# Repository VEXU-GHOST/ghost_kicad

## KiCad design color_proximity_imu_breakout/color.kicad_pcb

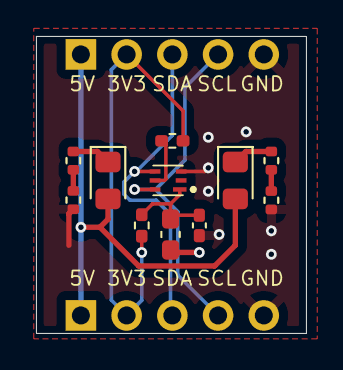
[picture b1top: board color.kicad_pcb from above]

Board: 2 copper layers, 15.0 x 16.5 mm, 13 parts (0 on the bottom side), 11 nets.

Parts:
C4: 1u; C_0603_1608Metric_Pad1.08x0.95mm_HandSolder
C5: 0.1u; C_0402_1005Metric_Pad0.74x0.62mm_HandSolder
D1, D2: WHITE; LED_0805_2012Metric_Pad1.15x1.40mm_HandSolder
IC2: ISL29125IROZ-T7; ISL29125IROZT7
J4, J4#2: Conn_01x05; PinHeader_1x05_P2.54mm_Vertical
R15: 100; R_0402_1005Metric_Pad0.72x0.64mm_HandSolder
R16: 4.7k; R_0402_1005Metric_Pad0.72x0.64mm_HandSolder
R17, R18, R30, R32: 120; R_0402_1005Metric

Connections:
+3.3V: J4.2, J4#2.2, R15.2, R16.1
+5V: D1.2 (A), D2.2 (A), J4.1, J4#2.1
/scl: IC2.6 (SCL), J4.4, J4#2.4
/sda: IC2.4 (SDA), J4.3, J4#2.3
GND: C4.2, C5.2, IC2.3 (GND), J4.5, J4#2.5, R30.2, R32.2
unnamed: D1.1 (K), R17.1
unnamed: D2.1 (K), R18.1
unnamed: C4.1, C5.1, IC2.1 (VDD), R15.1
unnamed: IC2.5 (~INT), R16.2
unnamed: R17.2, R30.1
unnamed: R18.2, R32.1

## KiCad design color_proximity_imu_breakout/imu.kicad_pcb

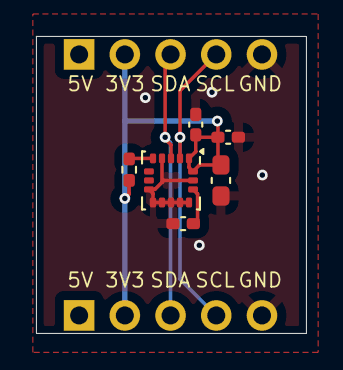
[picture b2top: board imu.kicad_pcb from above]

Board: 2 copper layers, 15.0 x 16.5 mm, 8 parts (0 on the bottom side), 7 nets.

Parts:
C7, C10: 0.1u; C_0402_1005Metric_Pad0.74x0.62mm_HandSolder
C8: 2.2u; C_0603_1608Metric_Pad1.08x0.95mm_HandSolder
C9: 10n; C_0402_1005Metric_Pad0.74x0.62mm_HandSolder
J4, J4#2: Conn_01x05; PinHeader_1x05_P2.54mm_Vertical
R19: 4.7k; R_0402_1005Metric_Pad0.72x0.64mm_HandSolder
U6: ICM-20602; LGA-16_3x3mm_P0.5mm_LayoutBorder3x5y

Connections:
+3.3V: C7.1, C8.1, C9.1, J4.2, J4#2.2, R19.1, U6.1 (VDDIO), U6.16 (VDD)
+5V: J4.1, J4#2.1
/scl: J4.4, J4#2.4, U6.2 (SCL/SPC)
/sda: J4.3, J4#2.3, U6.3 (SDA/SDI)
GND: C7.2, C8.2, C9.2, C10.2, J4.5, J4#2.5, U6.4 (SAO/SD0), U6.8 (FSYNC), U6.9 (GND), U6.10 (GND), U6.11 (GND), U6.12 (GND), U6.13 (GND), U6.15 (GND)
unnamed: C10.1, U6.14 (REGOUT)
unnamed: R19.2, U6.5 (~CS)

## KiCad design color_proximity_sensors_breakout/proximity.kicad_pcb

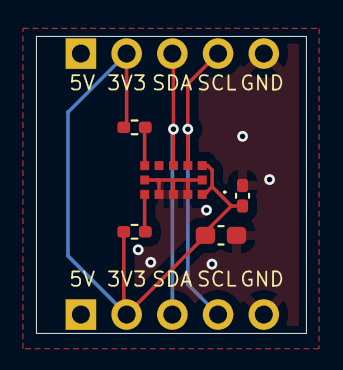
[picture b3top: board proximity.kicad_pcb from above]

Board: 2 copper layers, 15.0 x 16.5 mm, 7 parts (0 on the bottom side), 7 nets.

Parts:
C11: 0.1u; C_0402_1005Metric_Pad0.74x0.62mm_HandSolder
C12: 4.7u; C_0603_1608Metric_Pad1.08x0.95mm_HandSolder
IC1: VL53L4CDV0DH_1; VL53L4CDV0DH1
J4, J4#2: Conn_01x05; PinHeader_1x05_P2.54mm_Vertical
R20, R21: 10k; R_0402_1005Metric_Pad0.72x0.64mm_HandSolder

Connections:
+3.3V: C11.1, C12.1, IC1.1 (AVDDVCSEL_1), IC1.11 (AVDD), IC1.13 (AVDDVCSEL_2), J4.2, J4#2.2, R20.2, R21.1
+5V: J4.1, J4#2.1
/scl: IC1.10 (SCL), J4.4, J4#2.4
/sda: IC1.9 (SDA), J4.3, J4#2.3
GND: C11.2, C12.2, IC1.2 (AVSSVCSEL), IC1.3 (GND), IC1.4 (GND2), IC1.6 (GND3), IC1.12 (GND4), J4.5, J4#2.5
unnamed: IC1.7 (GPIO1), R20.1
unnamed: IC1.5 (XSHUT), R21.2

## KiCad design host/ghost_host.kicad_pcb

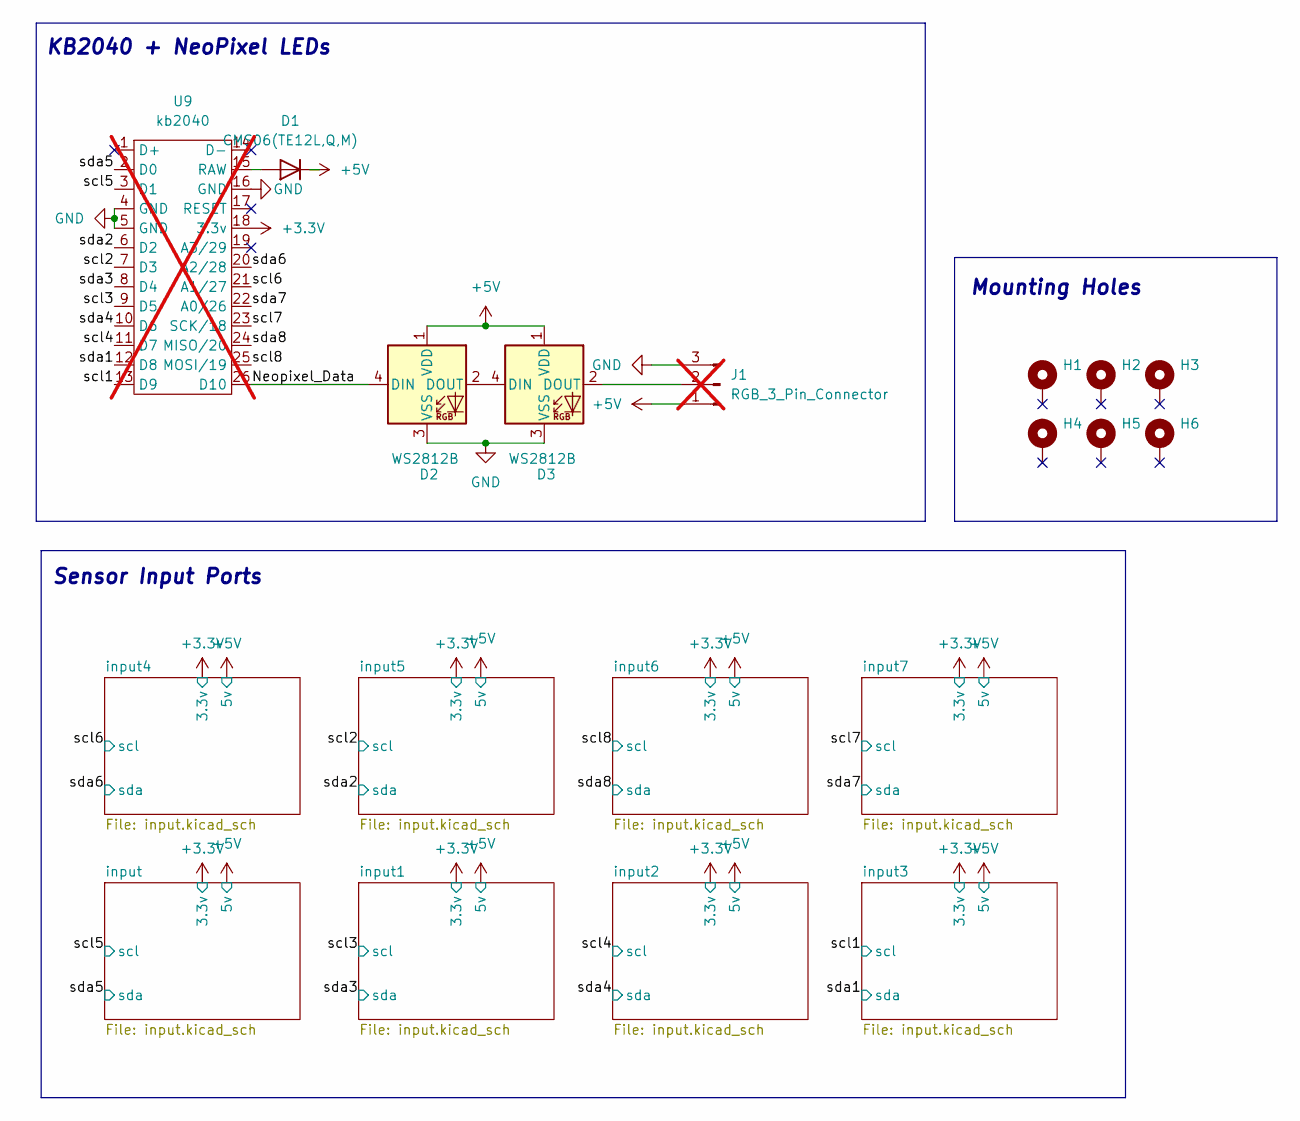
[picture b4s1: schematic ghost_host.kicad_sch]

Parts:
D1: CMS06(TE12L,Q,M); D_SOD-128; Manufacturer Part Number CMS06(TE12L,Q,M)
D2, D3: WS2812B; LED_WS2812B_PLCC4_5.0x5.0mm_P3.2mm; Manufacturer Part Number XL-5050RGBC-2812B
H1, H2, H3, H4, H5, H6: MountingHole_Pad; MountingHole_4.5mm_Pad_Via
J1: RGB_3_Pin_Connector; PinHeader_1x03_P2.54mm_Horizontal; not fitted
U9: kb2040; Manufacturer Part Number 5302; not fitted

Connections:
+3.3V: U9.18 (3.3v); also elsewhere on the board
+5V: D1.1 (K), D2.1 (VDD), D3.1 (VDD), J1.1; also elsewhere on the board
/Neopixel_Data: D2.4 (DIN), U9.26 (D10)
/scl1: U9.13 (D9); also elsewhere on the board
/scl2: U9.7 (D3); also elsewhere on the board
/scl3: U9.9 (D5); also elsewhere on the board
/scl4: U9.11 (D7); also elsewhere on the board
/scl5: U9.3 (D1); also elsewhere on the board
/scl6: U9.21 (A1/27); also elsewhere on the board
/scl7: U9.23 (SCK/18); also elsewhere on the board
/scl8: U9.25 (MOSI/19); also elsewhere on the board
/sda1: U9.12 (D8); also elsewhere on the board
/sda2: U9.6 (D2); also elsewhere on the board
/sda3: U9.8 (D4); also elsewhere on the board
/sda4: U9.10 (D6); also elsewhere on the board
/sda5: U9.2 (D0); also elsewhere on the board
/sda6: U9.20 (A2/28); also elsewhere on the board
/sda7: U9.22 (A0/26); also elsewhere on the board
/sda8: U9.24 (MISO/20); also elsewhere on the board
GND: D2.3 (VSS), D3.3 (VSS), J1.3, U9.4 (GND), U9.5 (GND), U9.16 (GND); also elsewhere on the board
unnamed: D1.2 (A), U9.15 (RAW)
unnamed: D2.2 (DOUT), D3.4 (DIN)
unnamed: D3.2 (DOUT), J1.2

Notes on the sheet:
KB2040 + NeoPixel LEDs
Mounting Holes
Sensor Input Ports

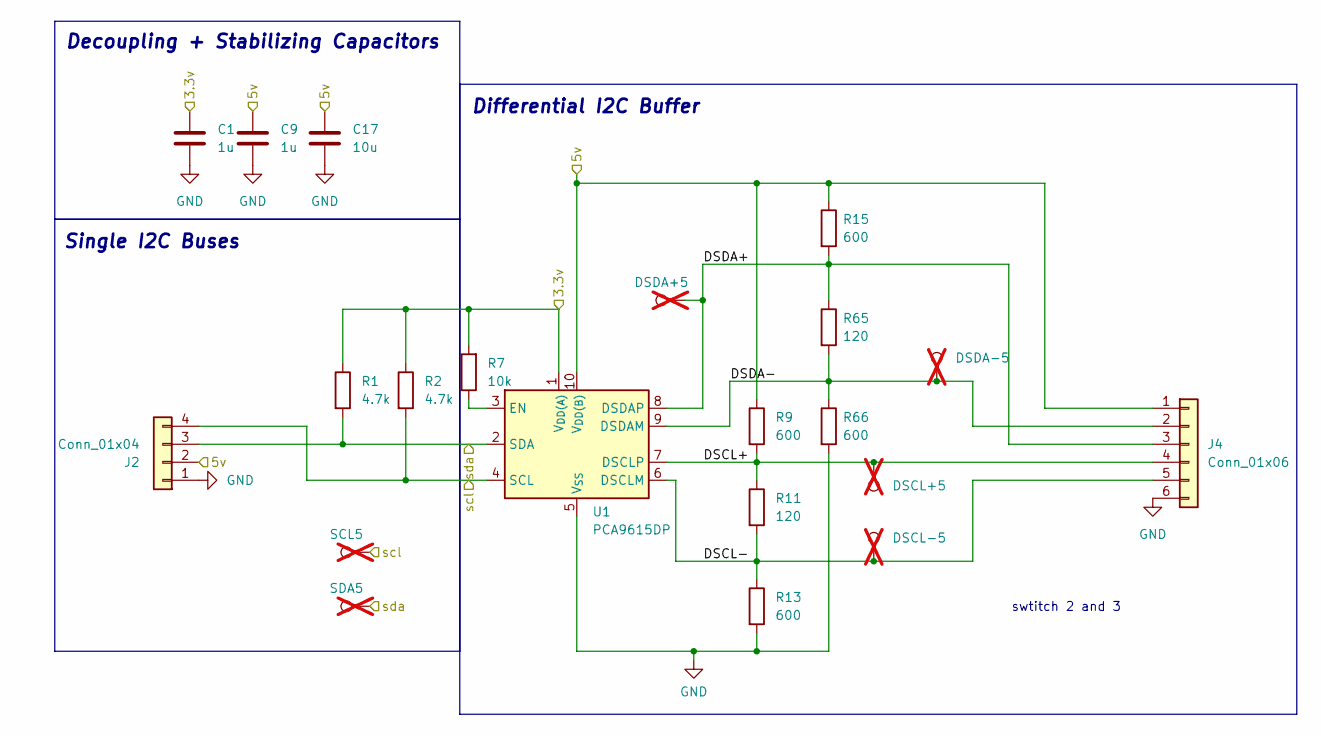
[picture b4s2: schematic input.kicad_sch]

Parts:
C1, C9: 1u; C_0603_1608Metric; Manufacturer Part Number CL10B105KB8NQNC
C17: 10u; C_0603_1608Metric; Manufacturer Part Number CL10A106KP8NNNC
DSCL+5: TestPoint; TestPoint_THTPad_1.0x1.0mm_Drill0.5mm; not fitted
DSCL-5: TestPoint; TestPoint_THTPad_1.0x1.0mm_Drill0.5mm; not fitted
DSDA+5: TestPoint; TestPoint_THTPad_1.0x1.0mm_Drill0.5mm; not fitted
DSDA-5: TestPoint; TestPoint_THTPad_1.0x1.0mm_Drill0.5mm; not fitted
J2: Conn_01x04; JST_GH_BM04B-GHS-TBT_1x04-1MP_P1.25mm_Vertical; Manufacturer Part Number BM04B-GHS-TBT(LF)(SN)
J4: Conn_01x06; JST_GH_SM06B-GHS-TB_1x06-1MP_P1.25mm_Horizontal; Manufacturer Part Number XY-SM06B-GHS-TB
R1, R2: 4.7k; R_0603_1608Metric_Pad0.98x0.95mm_HandSolder; Manufacturer Part Number 0603WAF4701T5E
R7: 10k; R_0603_1608Metric_Pad0.98x0.95mm_HandSolder; Manufacturer Part Number 0603WAF1002T5E
R9, R13, R15, R66: 600; R_0603_1608Metric_Pad0.98x0.95mm_HandSolder; Manufacturer Part Number 0603WAF5600T5E
R11, R65: 120; R_0603_1608Metric_Pad0.98x0.95mm_HandSolder; Manufacturer Part Number 0603WAF1200T5E
SCL5: TestPoint; TestPoint_THTPad_1.0x1.0mm_Drill0.5mm; not fitted
SDA5: TestPoint; TestPoint_THTPad_1.0x1.0mm_Drill0.5mm; not fitted
U1: PCA9615DP; TSSOP-10_3x3mm_P0.5mm; Manufacturer Part Number PCA9615DPZ

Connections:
+3.3V: C1.1, R1.1, R2.1, R7.2, U1.1 (V_{DD(A)}); also elsewhere on the board
+5V: C9.1, C17.1, J2.2, J4.1, R9.1, R15.1, U1.10 (V_{DD(B)}); also elsewhere on the board
/input/DSCL+: DSCL+5.1, J4.4, R9.2, R11.1, U1.7 (DSCLP)
/input/DSCL-: DSCL-5.1, J4.5, R11.2, R13.1, U1.6 (DSCLM)
/input/DSDA+: DSDA+5.1, J4.3, R15.2, R65.1, U1.8 (DSDAP)
/input/DSDA-: DSDA-5.1, J4.2, R65.2, R66.1, U1.9 (DSDAM)
/scl5: J2.4, R2.2, SCL5.1, U1.4 (SCL); also elsewhere on the board
/sda5: J2.3, R1.2, SDA5.1, U1.2 (SDA); also elsewhere on the board
GND: C1.2, C9.2, C17.2, J2.1, J4.6, R13.2, R66.2, U1.5 (V_{SS}); also elsewhere on the board
unnamed: R7.1, U1.3 (EN)

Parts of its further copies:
C2, C3, C4, C5, C6, C7, C8, C10, C11, C12, C13, C14, C15, C16: 1u; C_0603_1608Metric; Manufacturer Part Number CL10B105KB8NQNC
C18, C19, C20, C21, C22, C23, C24: 10u; C_0603_1608Metric; Manufacturer Part Number CL10A106KP8NNNC
DSCL+1, DSCL+2, DSCL+3, DSCL+4, DSCL+6, DSCL+7, DSCL+8: TestPoint; TestPoint_THTPad_1.0x1.0mm_Drill0.5mm; not fitted
DSCL-1, DSCL-2, DSCL-3, DSCL-4, DSCL-6, DSCL-7, DSCL-8: TestPoint; TestPoint_THTPad_1.0x1.0mm_Drill0.5mm; not fitted
DSDA+1, DSDA+2, DSDA+3, DSDA+4, DSDA+6, DSDA+7, DSDA+8: TestPoint; TestPoint_THTPad_1.0x1.0mm_Drill0.5mm; not fitted
DSDA-1, DSDA-2, DSDA-3, DSDA-4, DSDA-6, DSDA-7, DSDA-8: TestPoint; TestPoint_THTPad_1.0x1.0mm_Drill0.5mm; not fitted
J3, J5, J8, J11, J14, J17, J20: Conn_01x04; JST_GH_BM04B-GHS-TBT_1x04-1MP_P1.25mm_Vertical; Manufacturer Part Number BM04B-GHS-TBT(LF)(SN)
J6, J9, J12, J15, J18, J21, J23: Conn_01x06; JST_GH_SM06B-GHS-TB_1x06-1MP_P1.25mm_Horizontal; Manufacturer Part Number XY-SM06B-GHS-TB
R3, R14, R19, R21, R22, R24, R26, R28, R32, R34, R35, R37, R41, R43, R44, R46, R50, R52, R53, R55, R59, R61, R62, R64, R67, R69, R70, R72: 600; R_0603_1608Metric_Pad0.98x0.95mm_HandSolder; Manufacturer Part Number 0603WAF5600T5E
R4, R5, R8, R10, R16, R17, R29, R30, R38, R39, R47, R48, R56, R57: 4.7k; R_0603_1608Metric_Pad0.98x0.95mm_HandSolder; Manufacturer Part Number 0603WAF4701T5E
R6, R12, R18, R31, R40, R49, R58: 10k; R_0603_1608Metric_Pad0.98x0.95mm_HandSolder; Manufacturer Part Number 0603WAF1002T5E
R20, R23, R25, R27, R33, R36, R42, R45, R51, R54, R60, R63, R68, R71: 120; R_0603_1608Metric_Pad0.98x0.95mm_HandSolder; Manufacturer Part Number 0603WAF1200T5E
SCL1, SCL2, SCL3, SCL4, SCL6, SCL7, SCL8: TestPoint; TestPoint_THTPad_1.0x1.0mm_Drill0.5mm; not fitted
SDA1, SDA2, SDA3, SDA4, SDA6, SDA7, SDA8: TestPoint; TestPoint_THTPad_1.0x1.0mm_Drill0.5mm; not fitted
U2, U3, U4, U5, U6, U7, U8: PCA9615DP; TSSOP-10_3x3mm_P0.5mm; Manufacturer Part Number PCA9615DPZ

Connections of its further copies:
+3.3V: C2.1, C3.1, C4.1, C5.1, C6.1, C7.1, C8.1, R4.1, R5.1, R6.2, R8.1, R10.1, R12.2, R16.1, R17.1, R18.2, R29.1, R30.1, R31.2, R38.1, R39.1, R40.2, R47.1, R48.1, R49.2, R56.1, R57.1, R58.2, U2.1 (V_{DD(A)}), U3.1 (V_{DD(A)}), U4.1 (V_{DD(A)}), U5.1 (V_{DD(A)}), U6.1 (V_{DD(A)}), U7.1 (V_{DD(A)}), U8.1 (V_{DD(A)}); also elsewhere on the board
+5V: C10.1, C11.1, C12.1, C13.1, C14.1, C15.1, C16.1, C18.1, C19.1, C20.1, C21.1, C22.1, C23.1, C24.1, J3.2, J5.2, J6.1, J8.2, J9.1, J11.2, J12.1, J14.2, J15.1, J17.2, J18.1, J20.2, J21.1, J23.1, R3.1, R14.1, R19.1, R22.1, R32.1, R35.1, R41.1, R44.1, R50.1, R53.1, R59.1, R62.1, R67.1, R70.1, U2.10 (V_{DD(B)}), U3.10 (V_{DD(B)}), U4.10 (V_{DD(B)}), U5.10 (V_{DD(B)}), U6.10 (V_{DD(B)}), U7.10 (V_{DD(B)}), U8.10 (V_{DD(B)}); also elsewhere on the board
/input1/DSCL+: DSCL+2.1, J6.4, R67.2, R68.1, U2.7 (DSCLP)
/input1/DSCL-: DSCL-2.1, J6.5, R68.2, R69.1, U2.6 (DSCLM)
/input1/DSDA+: DSDA+2.1, J6.3, R70.2, R71.1, U2.8 (DSDAP)
/input1/DSDA-: DSDA-2.1, J6.2, R71.2, R72.1, U2.9 (DSDAM)
/input2/DSCL+: DSCL+3.1, J9.4, R19.2, R20.1, U3.7 (DSCLP)
/input2/DSCL-: DSCL-3.1, J9.5, R20.2, R21.1, U3.6 (DSCLM)
/input2/DSDA+: DSDA+3.1, J9.3, R22.2, R23.1, U3.8 (DSDAP)
/input2/DSDA-: DSDA-3.1, J9.2, R23.2, R24.1, U3.9 (DSDAM)
/input3/DSCL+: DSCL+4.1, J12.4, R14.2, R25.1, U4.7 (DSCLP)
/input3/DSCL-: DSCL-4.1, J12.5, R25.2, R26.1, U4.6 (DSCLM)
/input3/DSDA+: DSDA+4.1, J12.3, R3.2, R27.1, U4.8 (DSDAP)
/input3/DSDA-: DSDA-4.1, J12.2, R27.2, R28.1, U4.9 (DSDAM)
/input4/DSCL+: DSCL+6.1, J15.4, R32.2, R33.1, U5.7 (DSCLP)
/input4/DSCL-: DSCL-6.1, J15.5, R33.2, R34.1, U5.6 (DSCLM)
/input4/DSDA+: DSDA+6.1, J15.3, R35.2, R36.1, U5.8 (DSDAP)
/input4/DSDA-: DSDA-6.1, J15.2, R36.2, R37.1, U5.9 (DSDAM)
/input5/DSCL+: DSCL+1.1, J18.4, R41.2, R42.1, U6.7 (DSCLP)
/input5/DSCL-: DSCL-1.1, J18.5, R42.2, R43.1, U6.6 (DSCLM)
/input5/DSDA+: DSDA+1.1, J18.3, R44.2, R45.1, U6.8 (DSDAP)
/input5/DSDA-: DSDA-1.1, J18.2, R45.2, R46.1, U6.9 (DSDAM)
/input6/DSCL+: DSCL+8.1, J21.4, R50.2, R51.1, U7.7 (DSCLP)
/input6/DSCL-: DSCL-8.1, J21.5, R51.2, R52.1, U7.6 (DSCLM)
/input6/DSDA+: DSDA+8.1, J21.3, R53.2, R54.1, U7.8 (DSDAP)
/input6/DSDA-: DSDA-8.1, J21.2, R54.2, R55.1, U7.9 (DSDAM)
/input7/DSCL+: DSCL+7.1, J23.4, R59.2, R60.1, U8.7 (DSCLP)
/input7/DSCL-: DSCL-7.1, J23.5, R60.2, R61.1, U8.6 (DSCLM)
/input7/DSDA+: DSDA+7.1, J23.3, R62.2, R63.1, U8.8 (DSDAP)
/input7/DSDA-: DSDA-7.1, J23.2, R63.2, R64.1, U8.9 (DSDAM)
/scl1: J8.4, R10.2, SCL4.1, U4.4 (SCL); also elsewhere on the board
/scl2: J14.4, R39.2, SCL1.1, U6.4 (SCL); also elsewhere on the board
/scl3: J3.4, R5.2, SCL2.1, U2.4 (SCL); also elsewhere on the board
/scl4: J5.4, R17.2, SCL3.1, U3.4 (SCL); also elsewhere on the board
/scl6: J11.4, R30.2, SCL6.1, U5.4 (SCL); also elsewhere on the board
/scl7: J20.4, R57.2, SCL7.1, U8.4 (SCL); also elsewhere on the board
/scl8: J17.4, R48.2, SCL8.1, U7.4 (SCL); also elsewhere on the board
/sda1: J8.3, R8.2, SDA4.1, U4.2 (SDA); also elsewhere on the board
/sda2: J14.3, R38.2, SDA1.1, U6.2 (SDA); also elsewhere on the board
/sda3: J3.3, R4.2, SDA2.1, U2.2 (SDA); also elsewhere on the board
/sda4: J5.3, R16.2, SDA3.1, U3.2 (SDA); also elsewhere on the board
/sda6: J11.3, R29.2, SDA6.1, U5.2 (SDA); also elsewhere on the board
/sda7: J20.3, R56.2, SDA7.1, U8.2 (SDA); also elsewhere on the board
/sda8: J17.3, R47.2, SDA8.1, U7.2 (SDA); also elsewhere on the board
GND: C2.2, C3.2, C4.2, C5.2, C6.2, C7.2, C8.2, C10.2, C11.2, C12.2, C13.2, C14.2, C15.2, C16.2, C18.2, C19.2, C20.2, C21.2, C22.2, C23.2, C24.2, J3.1, J5.1, J6.6, J8.1, J9.6, J11.1, J12.6, J14.1, J15.6, J17.1, J18.6, J20.1, J21.6, J23.6, R21.2, R24.2, R26.2, R28.2, R34.2, R37.2, R43.2, R46.2, R52.2, R55.2, R61.2, R64.2, R69.2, R72.2, U2.5 (V_{SS}), U3.5 (V_{SS}), U4.5 (V_{SS}), U5.5 (V_{SS}), U6.5 (V_{SS}), U7.5 (V_{SS}), U8.5 (V_{SS}); also elsewhere on the board
unnamed: R6.1, U2.3 (EN)
unnamed: R18.1, U3.3 (EN)
unnamed: R12.1, U4.3 (EN)
unnamed: R31.1, U5.3 (EN)
unnamed: R40.1, U6.3 (EN)
unnamed: R49.1, U7.3 (EN)
unnamed: R58.1, U8.3 (EN)

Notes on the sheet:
swtitch 2 and 3
Single I2C Buses
Decoupling + Stabilizing Capacitors
Differential I2C Buffer

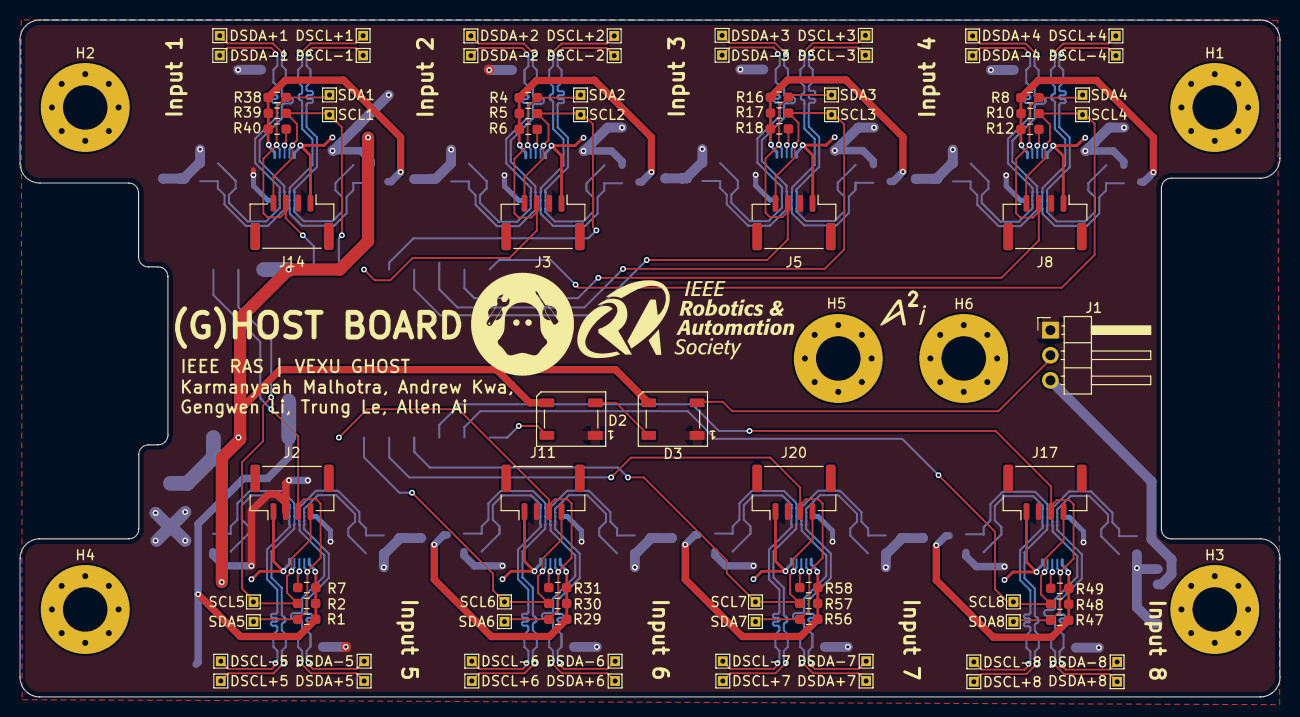
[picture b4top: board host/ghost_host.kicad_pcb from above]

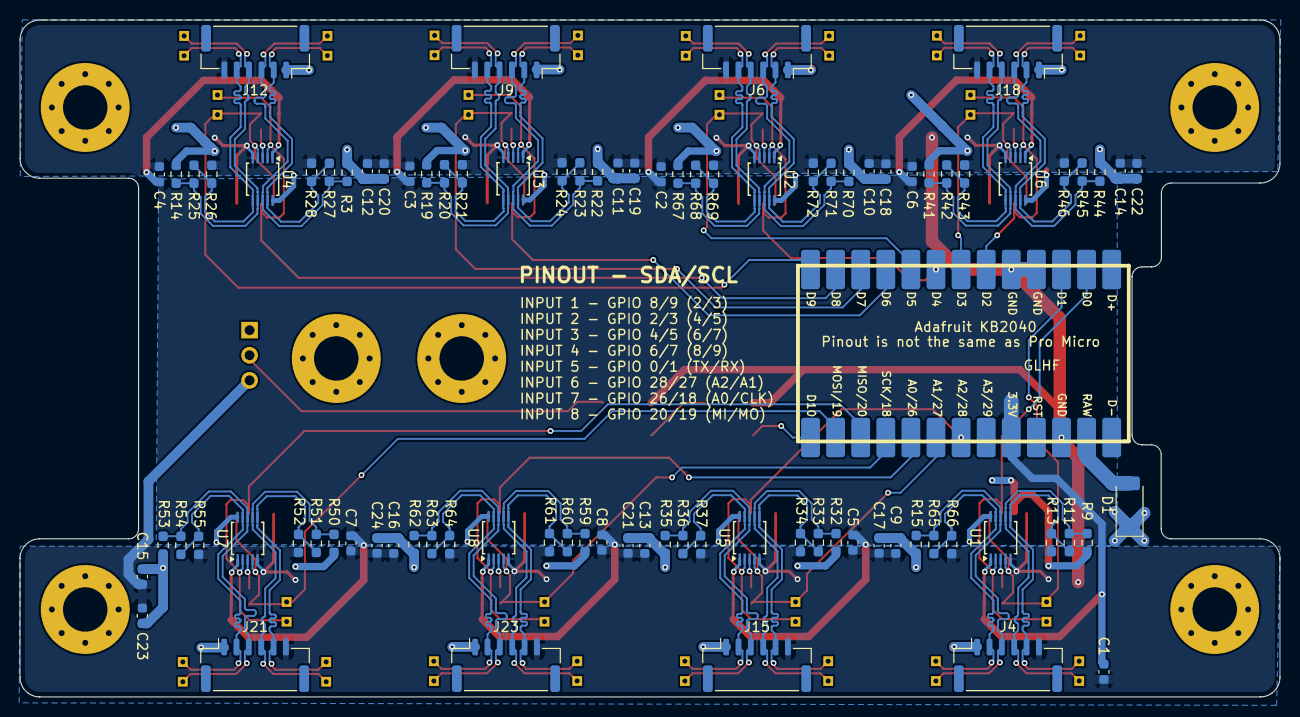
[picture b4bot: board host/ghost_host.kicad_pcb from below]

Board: 2 copper layers, 127.5 x 68.5 mm, 179 parts (90 on the bottom side), 63 nets.

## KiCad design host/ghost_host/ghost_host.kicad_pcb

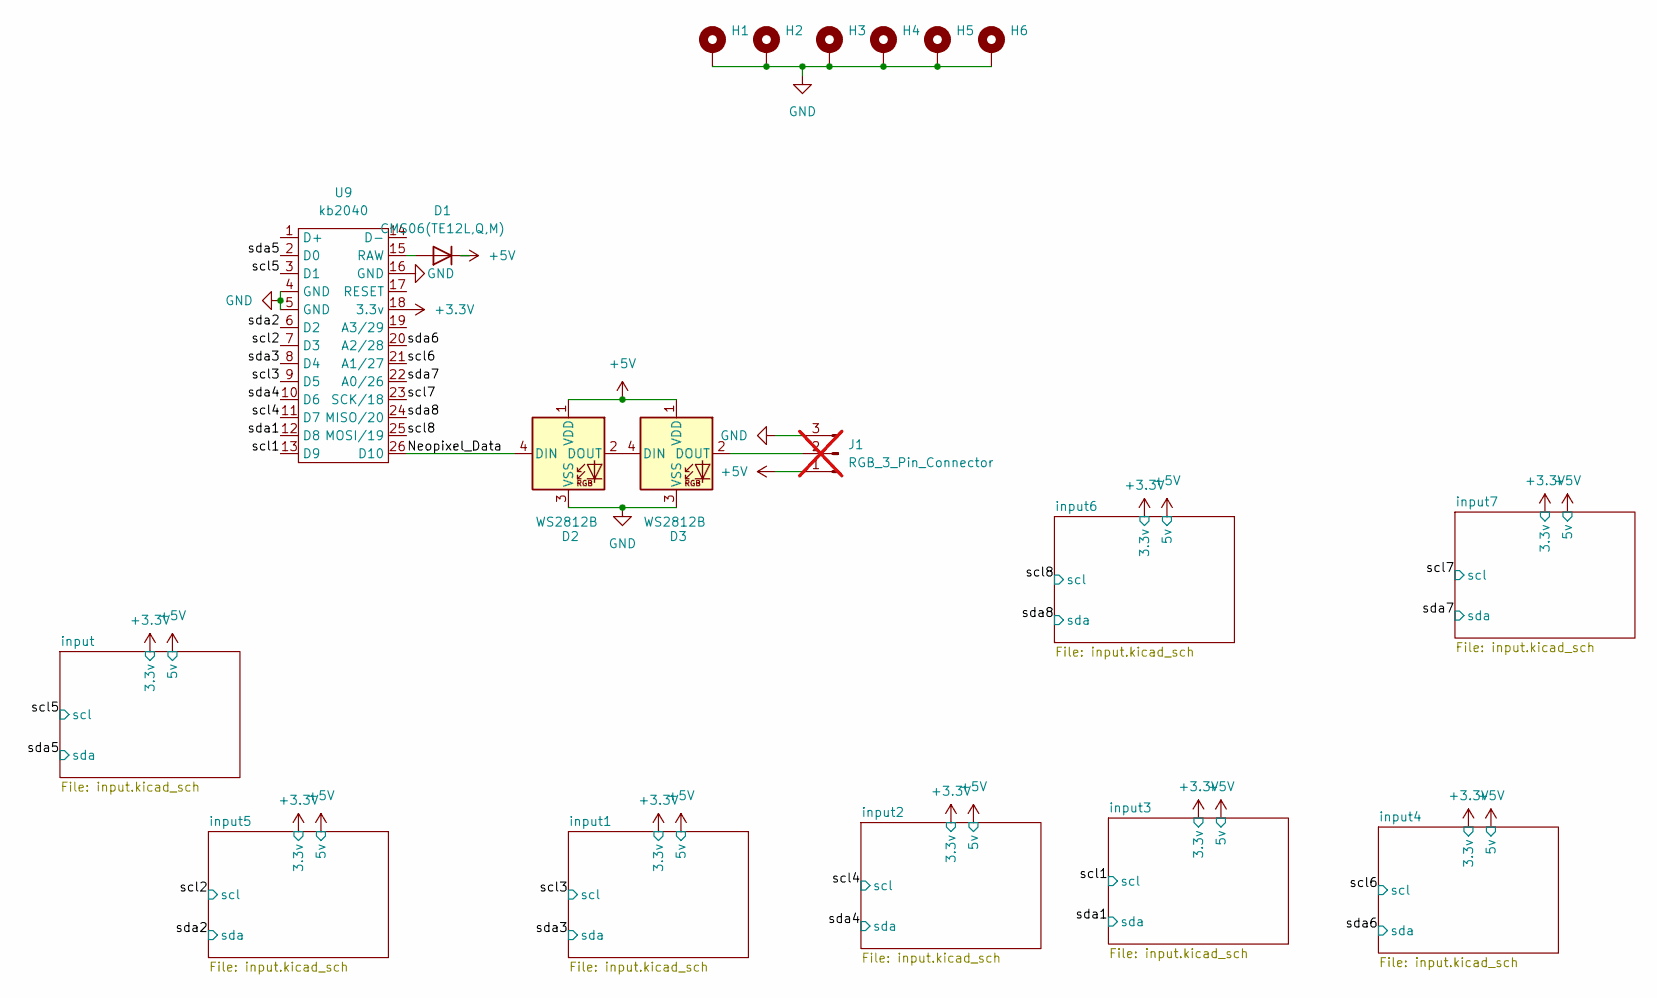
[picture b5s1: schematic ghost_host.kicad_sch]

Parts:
D1: CMS06(TE12L,Q,M); D_SOD-323_HandSoldering
D2, D3: WS2812B; LED_WS2812B_PLCC4_5.0x5.0mm_P3.2mm
H1, H2, H3, H4, H5, H6: MountingHole_Pad; MountingHole_4.5mm_Pad_Via
J1: RGB_3_Pin_Connector; PinHeader_1x03_P2.54mm_Horizontal; not fitted
U9: kb2040

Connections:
+3.3V: U9.18 (3.3v); also elsewhere on the board
+5V: D1.1 (K), D2.1 (VDD), D3.1 (VDD), J1.1; also elsewhere on the board
/Neopixel_Data: D2.4 (DIN), U9.26 (D10)
/scl1: U9.13 (D9); also elsewhere on the board
/scl2: U9.7 (D3); also elsewhere on the board
/scl3: U9.9 (D5); also elsewhere on the board
/scl4: U9.11 (D7); also elsewhere on the board
/scl5: U9.3 (D1); also elsewhere on the board
/scl6: U9.21 (A1/27); also elsewhere on the board
/scl7: U9.23 (SCK/18); also elsewhere on the board
/scl8: U9.25 (MOSI/19); also elsewhere on the board
/sda1: U9.12 (D8); also elsewhere on the board
/sda2: U9.6 (D2); also elsewhere on the board
/sda3: U9.8 (D4); also elsewhere on the board
/sda4: U9.10 (D6); also elsewhere on the board
/sda5: U9.2 (D0); also elsewhere on the board
/sda6: U9.20 (A2/28); also elsewhere on the board
/sda7: U9.22 (A0/26); also elsewhere on the board
/sda8: U9.24 (MISO/20); also elsewhere on the board
GND: D2.3 (VSS), D3.3 (VSS), H1.1, H2.1, H3.1, H4.1, H5.1, H6.1, J1.3, U9.4 (GND), U9.5 (GND), U9.16 (GND); also elsewhere on the board
unnamed: D1.2 (A), U9.15 (RAW)
unnamed: D2.2 (DOUT), D3.4 (DIN)
unnamed: D3.2 (DOUT), J1.2

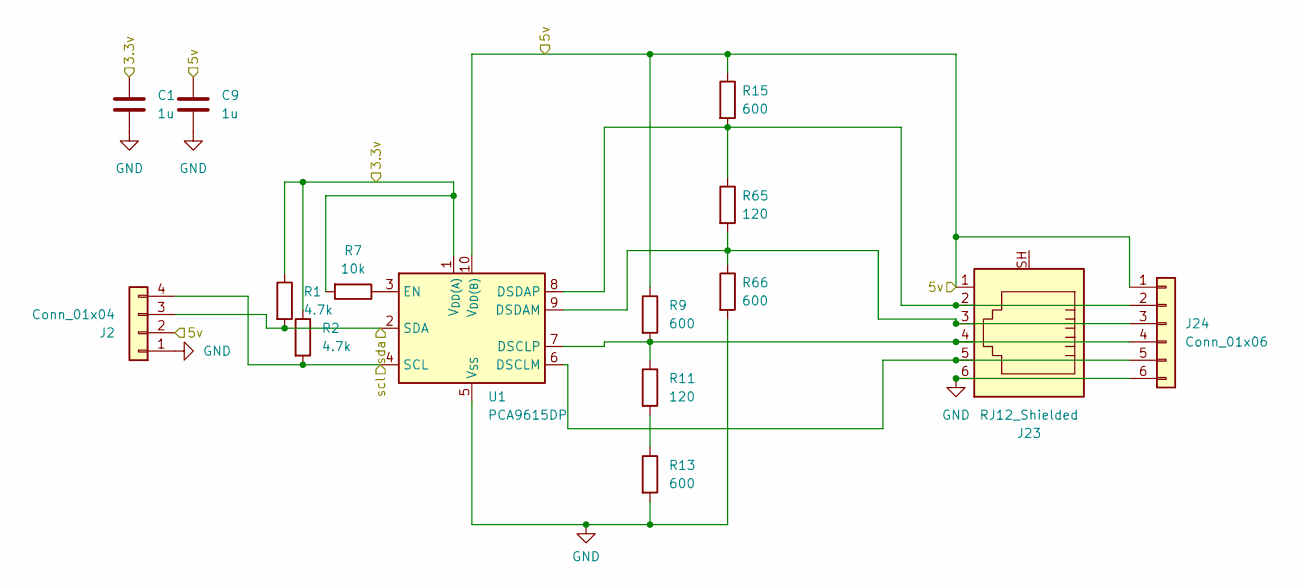
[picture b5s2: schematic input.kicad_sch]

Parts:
C1, C9: 1u; C_0603_1608Metric
J2: Conn_01x04; JST_SH_BM04B-SRSS-TB_1x04-1MP_P1.00mm_Vertical; Manufacturer Part Number BM04B-SRSS-TB(LF)(SN)
J23: RJ12_Shielded; RJ12_Pin_Connector; Manufacturer Part Number 5201-660111
J24: Conn_01x06; JST_SH_BM06B-SRSS-TB_1x06-1MP_P1.00mm_Vertical; Manufacturer Part Number BM06B-SRSS-TB(LF)(SN)
R1, R2: 4.7k; R_0603_1608Metric_Pad0.98x0.95mm_HandSolder; Manufacturer Part Number 0603WAF4701T5E
R7: 10k; R_0603_1608Metric_Pad0.98x0.95mm_HandSolder; Manufacturer Part Number 0603WAF1002T5E
R9, R13, R15, R66: 600; R_0603_1608Metric_Pad0.98x0.95mm_HandSolder; Manufacturer Part Number 0603WAF5600T5E
R11, R65: 120; R_0603_1608Metric_Pad0.98x0.95mm_HandSolder; Manufacturer Part Number 0603WAF1200T5E
U1: PCA9615DP; TSSOP-10_3x3mm_P0.5mm; Manufacturer Part Number PCA9615DPZ

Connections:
+3.3V: C1.1, R1.1, R2.1, R7.2, U1.1 (V_{DD(A)}); also elsewhere on the board
+5V: C9.1, J2.2, J23.1, J24.1, R9.1, R15.1, U1.10 (V_{DD(B)}); also elsewhere on the board
/scl5: J2.4, R2.2, U1.4 (SCL); also elsewhere on the board
/sda5: J2.3, R1.2, U1.2 (SDA); also elsewhere on the board
GND: C1.2, C9.2, J2.1, J23.6, J24.6, R13.2, R66.2, U1.5 (V_{SS}); also elsewhere on the board
unnamed: J23.2, J24.2, R15.2, R65.1, U1.8 (DSDAP)
unnamed: J23.3, J24.3, R65.2, R66.1, U1.9 (DSDAM)
unnamed: J23.4, J24.4, R9.2, R11.1, U1.7 (DSCLP)
unnamed: J23.5, J24.5, U1.6 (DSCLM)
unnamed: R11.2, R13.1
unnamed: R7.1, U1.3 (EN)

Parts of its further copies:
C2, C3, C4, C5, C6, C7, C8, C10, C11, C12, C13, C14, C15, C16: 1u; C_0603_1608Metric
J3, J5, J8, J11, J14, J17, J20: Conn_01x04; JST_SH_BM04B-SRSS-TB_1x04-1MP_P1.00mm_Vertical; Manufacturer Part Number BM04B-SRSS-TB(LF)(SN)
J4, J6, J9, J12, J15, J18, J21: RJ12_Shielded; RJ12_Pin_Connector; Manufacturer Part Number 5201-660111
J7, J10, J13, J16, J19, J22, J25: Conn_01x06; JST_SH_BM06B-SRSS-TB_1x06-1MP_P1.00mm_Vertical; Manufacturer Part Number BM06B-SRSS-TB(LF)(SN)
R3, R14, R19, R21, R22, R24, R26, R28, R32, R34, R35, R37, R41, R43, R44, R46, R50, R52, R53, R55, R59, R61, R62, R64, R67, R69, R70, R72: 600; R_0603_1608Metric_Pad0.98x0.95mm_HandSolder; Manufacturer Part Number 0603WAF5600T5E
R4, R5, R8, R10, R16, R17, R29, R30, R38, R39, R47, R48, R56, R57: 4.7k; R_0603_1608Metric_Pad0.98x0.95mm_HandSolder; Manufacturer Part Number 0603WAF4701T5E
R6, R12, R18, R31, R40, R49, R58: 10k; R_0603_1608Metric_Pad0.98x0.95mm_HandSolder; Manufacturer Part Number 0603WAF1002T5E
R20, R23, R25, R27, R33, R36, R42, R45, R51, R54, R60, R63, R68, R71: 120; R_0603_1608Metric_Pad0.98x0.95mm_HandSolder; Manufacturer Part Number 0603WAF1200T5E
U2, U3, U4, U5, U6, U7, U8: PCA9615DP; TSSOP-10_3x3mm_P0.5mm; Manufacturer Part Number PCA9615DPZ

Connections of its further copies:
+3.3V: C2.1, C3.1, C4.1, C5.1, C6.1, C7.1, C8.1, R4.1, R5.1, R6.2, R8.1, R10.1, R12.2, R16.1, R17.1, R18.2, R29.1, R30.1, R31.2, R38.1, R39.1, R40.2, R47.1, R48.1, R49.2, R56.1, R57.1, R58.2, U2.1 (V_{DD(A)}), U3.1 (V_{DD(A)}), U4.1 (V_{DD(A)}), U5.1 (V_{DD(A)}), U6.1 (V_{DD(A)}), U7.1 (V_{DD(A)}), U8.1 (V_{DD(A)}); also elsewhere on the board
+5V: C10.1, C11.1, C12.1, C13.1, C14.1, C15.1, C16.1, J3.2, J4.1, J5.2, J6.1, J7.1, J8.2, J9.1, J10.1, J11.2, J12.1, J13.1, J14.2, J15.1, J16.1, J17.2, J18.1, J19.1, J20.2, J21.1, J22.1, J25.1, R3.1, R14.1, R19.1, R22.1, R32.1, R35.1, R41.1, R44.1, R50.1, R53.1, R59.1, R62.1, R67.1, R70.1, U2.10 (V_{DD(B)}), U3.10 (V_{DD(B)}), U4.10 (V_{DD(B)}), U5.10 (V_{DD(B)}), U6.10 (V_{DD(B)}), U7.10 (V_{DD(B)}), U8.10 (V_{DD(B)}); also elsewhere on the board
/scl1: J8.4, R10.2, U4.4 (SCL); also elsewhere on the board
/scl2: J14.4, R39.2, U6.4 (SCL); also elsewhere on the board
/scl3: J3.4, R5.2, U2.4 (SCL); also elsewhere on the board
/scl4: J5.4, R17.2, U3.4 (SCL); also elsewhere on the board
/scl6: J11.4, R30.2, U5.4 (SCL); also elsewhere on the board
/scl7: J20.4, R57.2, U8.4 (SCL); also elsewhere on the board
/scl8: J17.4, R48.2, U7.4 (SCL); also elsewhere on the board
/sda1: J8.3, R8.2, U4.2 (SDA); also elsewhere on the board
/sda2: J14.3, R38.2, U6.2 (SDA); also elsewhere on the board
/sda3: J3.3, R4.2, U2.2 (SDA); also elsewhere on the board
/sda4: J5.3, R16.2, U3.2 (SDA); also elsewhere on the board
/sda6: J11.3, R29.2, U5.2 (SDA); also elsewhere on the board
/sda7: J20.3, R56.2, U8.2 (SDA); also elsewhere on the board
/sda8: J17.3, R47.2, U7.2 (SDA); also elsewhere on the board
GND: C2.2, C3.2, C4.2, C5.2, C6.2, C7.2, C8.2, C10.2, C11.2, C12.2, C13.2, C14.2, C15.2, C16.2, J3.1, J4.6, J5.1, J6.6, J7.6, J8.1, J9.6, J10.6, J11.1, J12.6, J13.6, J14.1, J15.6, J16.6, J17.1, J18.6, J19.6, J20.1, J21.6, J22.6, J25.6, R21.2, R24.2, R26.2, R28.2, R34.2, R37.2, R43.2, R46.2, R52.2, R55.2, R61.2, R64.2, R69.2, R72.2, U2.5 (V_{SS}), U3.5 (V_{SS}), U4.5 (V_{SS}), U5.5 (V_{SS}), U6.5 (V_{SS}), U7.5 (V_{SS}), U8.5 (V_{SS}); also elsewhere on the board
unnamed: J6.2, J7.2, R22.2, R23.1, U3.8 (DSDAP)
unnamed: J6.3, J7.3, R23.2, R24.1, U3.9 (DSDAM)
unnamed: J6.4, J7.4, R19.2, R20.1, U3.7 (DSCLP)
unnamed: J6.5, J7.5, U3.6 (DSCLM)
unnamed: J9.2, J10.2, R3.2, R27.1, U4.8 (DSDAP)
unnamed: J9.3, J10.3, R27.2, R28.1, U4.9 (DSDAM)
unnamed: J9.4, J10.4, R14.2, R25.1, U4.7 (DSCLP)
unnamed: J9.5, J10.5, U4.6 (DSCLM)
unnamed: J12.2, J13.2, R35.2, R36.1, U5.8 (DSDAP)
unnamed: J12.3, J13.3, R36.2, R37.1, U5.9 (DSDAM)
unnamed: J12.4, J13.4, R32.2, R33.1, U5.7 (DSCLP)
unnamed: J12.5, J13.5, U5.6 (DSCLM)
unnamed: J15.2, J16.2, R44.2, R45.1, U6.8 (DSDAP)
unnamed: J15.3, J16.3, R45.2, R46.1, U6.9 (DSDAM)
unnamed: J15.4, J16.4, R41.2, R42.1, U6.7 (DSCLP)
unnamed: J15.5, J16.5, U6.6 (DSCLM)
unnamed: J18.2, J19.2, R53.2, R54.1, U7.8 (DSDAP)
unnamed: J18.3, J19.3, R54.2, R55.1, U7.9 (DSDAM)
unnamed: J18.4, J19.4, R50.2, R51.1, U7.7 (DSCLP)
unnamed: J18.5, J19.5, U7.6 (DSCLM)
unnamed: J21.2, J22.2, R62.2, R63.1, U8.8 (DSDAP)
unnamed: J21.3, J22.3, R63.2, R64.1, U8.9 (DSDAM)
unnamed: J21.4, J22.4, R59.2, R60.1, U8.7 (DSCLP)
unnamed: J21.5, J22.5, U8.6 (DSCLM)
unnamed: J4.2, J25.2, R70.2, R71.1, U2.8 (DSDAP)
unnamed: J4.3, J25.3, R71.2, R72.1, U2.9 (DSDAM)
unnamed: J4.4, J25.4, R67.2, R68.1, U2.7 (DSCLP)
unnamed: J4.5, J25.5, U2.6 (DSCLM)
unnamed: R20.2, R21.1
unnamed: R25.2, R26.1
unnamed: R33.2, R34.1
unnamed: R42.2, R43.1
unnamed: R51.2, R52.1
unnamed: R60.2, R61.1
unnamed: R68.2, R69.1
unnamed: R6.1, U2.3 (EN)
unnamed: R18.1, U3.3 (EN)
unnamed: R12.1, U4.3 (EN)
unnamed: R31.1, U5.3 (EN)
unnamed: R40.1, U6.3 (EN)
unnamed: R49.1, U7.3 (EN)
unnamed: R58.1, U8.3 (EN)

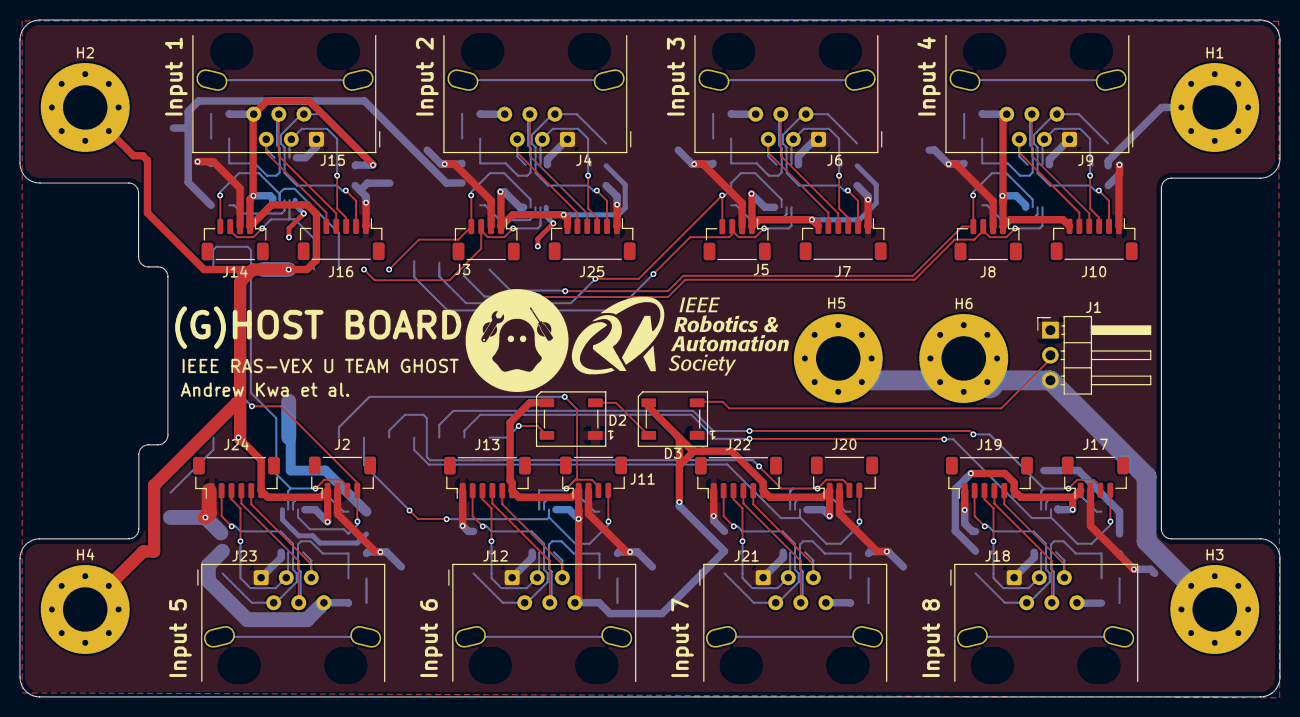
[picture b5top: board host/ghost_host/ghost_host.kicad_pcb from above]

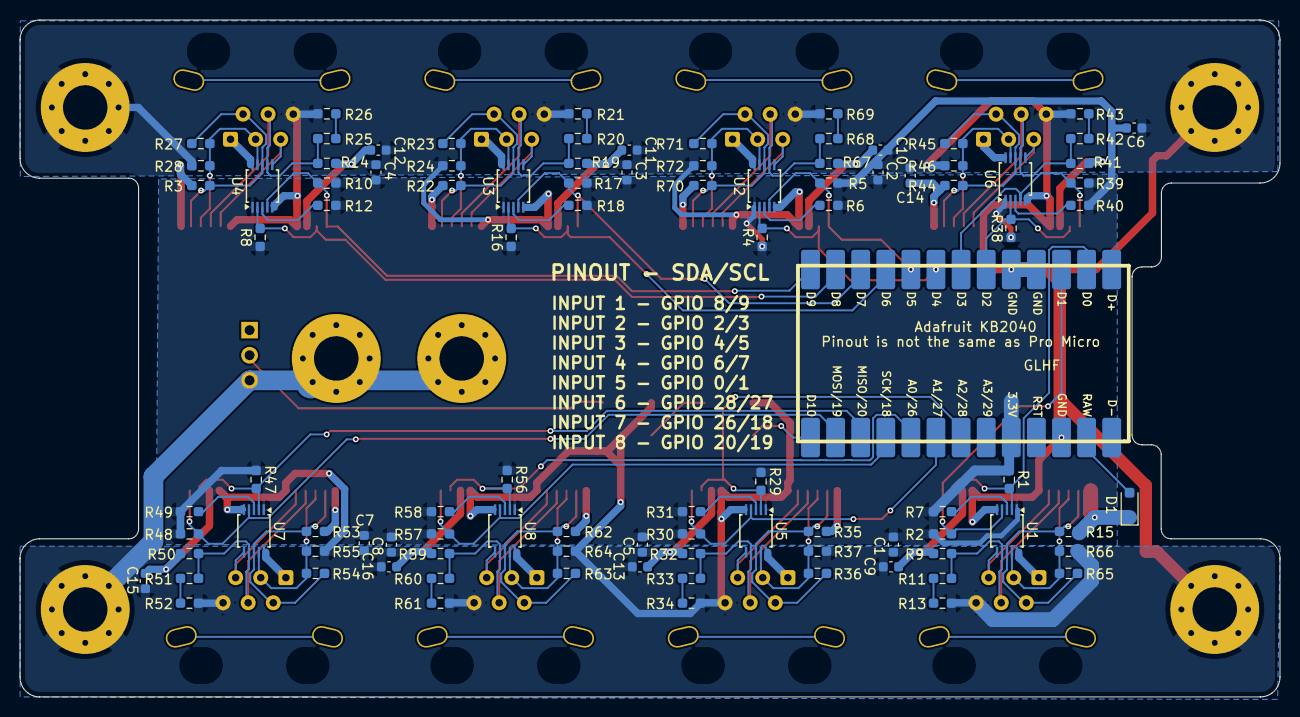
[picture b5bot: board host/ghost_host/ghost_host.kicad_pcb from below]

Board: 2 copper layers, 127.5 x 68.5 mm, 131 parts (98 on the bottom side), 71 nets.
